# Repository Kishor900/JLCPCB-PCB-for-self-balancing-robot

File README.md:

# Self Balancing Robot PCB Board Powered by JLCPCB.COM
This repo conists of robotics project NON-Arduino version Self balancing robot PCB

# How to upload ?
1. Clone or download the gerber file from this repo
2. Open jlcpcb.com
3. Click `Quote Now` button and 
4. Click `Add you gerber file`
5. Everything is prettymuch ok if your settings are just decent enough
6. Select shipping method and add to cart

# Verification
JLCPCB professional team will verify your gerber files within an hour

Once verified they will ship your order that should reach you within 10-15 working days

# How to modify schematic and brd ?
To edit my schematic you are going to need Autodesk Eagle CAD software. Once installed, open my brd and schematic file and import them to a project.

Thank you :)

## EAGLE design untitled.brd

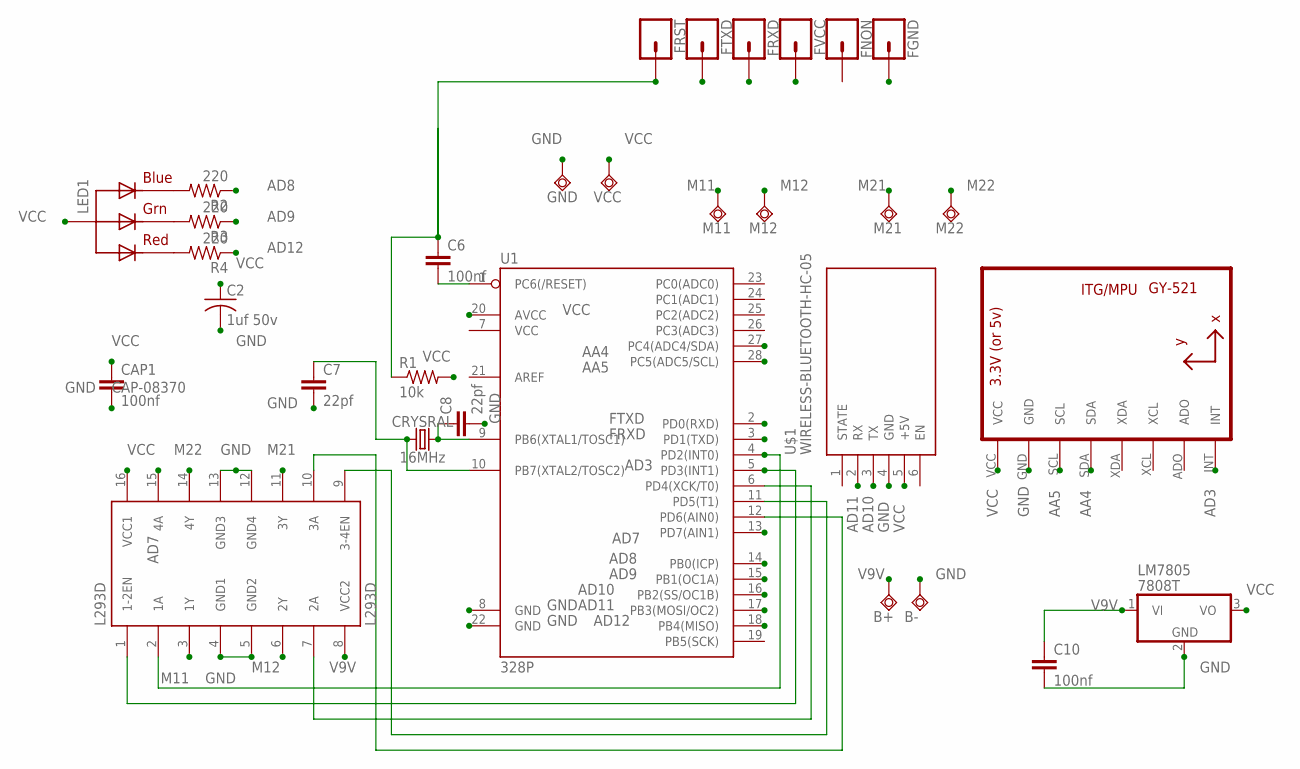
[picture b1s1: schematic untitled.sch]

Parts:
B+: TESTPAD_TPSQPAD1-20Y; TESTPAD_P1-20Y
B-: TESTPAD_TPSQPAD1-20Y; TESTPAD_P1-20Y
C2: 1uf 50v; C025-024X044
C6, C10: 100nf; CAP-PTH-SMALL-KIT
C7, C8: 22pf; CAP-PTH-SMALL-KIT
CAP1: 100nf; CAP-PTH-SMALL-KIT
CRYSRAL: 16MHz; HC49US
FGND: CONN_01; 1X01
FNON: CONN_01; 1X01
FRST: CONN_01; 1X01
FRXD: CONN_01; 1X01
FTXD: CONN_01; 1X01
FVCC: CONN_01; 1X01
GND: TESTPAD_TPSQB2,54; TESTPAD_B2,54
L293D: L293D; DIL16
LED1: RGBLED_CA-PIRANHA; PIRANHA5MM
LM7805: 7808T; TO220H
M11, M12, M21, M22: TESTPAD_TPSQPAD1-13; TESTPAD_P1-13
R1: 10k; 0204/7
R2, R3, R4: 220; 0204/7
U1: 328P; DIP28
U2: GY-521MPU6050; GY-521
U$1: WIRELESS-BLUETOOTH-HC-05
VCC: TESTPAD_TPSQB2,54; TESTPAD_B2,54

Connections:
AA4: U1.27 (PC4(ADC4/SDA)), U2.SDA
AA5: U1.28 (PC5(ADC5/SCL)), U2.SCL
AD3: L293D.1 (1-2EN), U1.5 (PD3(INT1)), U2.INT
AD7: L293D.15 (4A), U1.13 (PD7(AIN1))
AD8: R2.1, U1.14 (PB0(ICP))
AD9: R3.1, U1.15 (PB1(OC1A))
AD10: U1.16 (PB2(SS/OC1B)), U$1.3 (TX)
AD11: U1.17 (PB3(MOSI/OC2)), U$1.2 (RX)
AD12: R4.1, U1.18 (PB4(MISO))
FRXD: FRXD.1, U1.3 (PD1(TXD))
FTXD: FTXD.1, U1.2 (PD0(RXD))
GND: B-.TP, C2.2, C7.2, C8.2, C10.2, CAP1.2, FGND.1, GND.TP, L293D.4 (GND1), L293D.5 (GND2), L293D.12 (GND4), L293D.13 (GND3), LM7805.2 (GND), U1.8 (GND), U1.22 (GND), U2.GND, U$1.4 (GND)
M11: L293D.3 (1Y), M11.TP
M12: L293D.6 (2Y), M12.TP
M21: L293D.11 (3Y), M21.TP
M22: L293D.14 (4Y), M22.TP
unnamed: C6.2, U1.1 (PC6(/RESET))
unnamed: L293D.2 (1A), U1.4 (PD2(INT0))
unnamed: LED1.1 (BLUE), R2.2
unnamed: L293D.7 (2A), U1.6 (PD4(XCK/T0))
unnamed: C8.1, CRYSRAL.2, U1.9 (PB6(XTAL1/TOSC1))
unnamed: C7.1, CRYSRAL.1, U1.10 (PB7(XTAL2/TOSC2))
unnamed: L293D.9 (3-4EN), U1.11 (PD5(T1))
unnamed: L293D.10 (3A), U1.12 (PD6(AIN0))
unnamed: LED1.2 (RED), R4.2
unnamed: LED1.3 (GREEN), R3.2
unnamed: C6.1, FRST.1, R1.1
V9V: B+.TP, C10.1, L293D.8 (VCC2), LM7805.1 (VI)
VCC: C2.1, CAP1.1, FVCC.1, L293D.16 (VCC1), LED1.4 (VCC), LM7805.3 (VO), R1.2, U1.20 (AVCC), U2.VCC, U$1.5 (+5V), VCC.TP

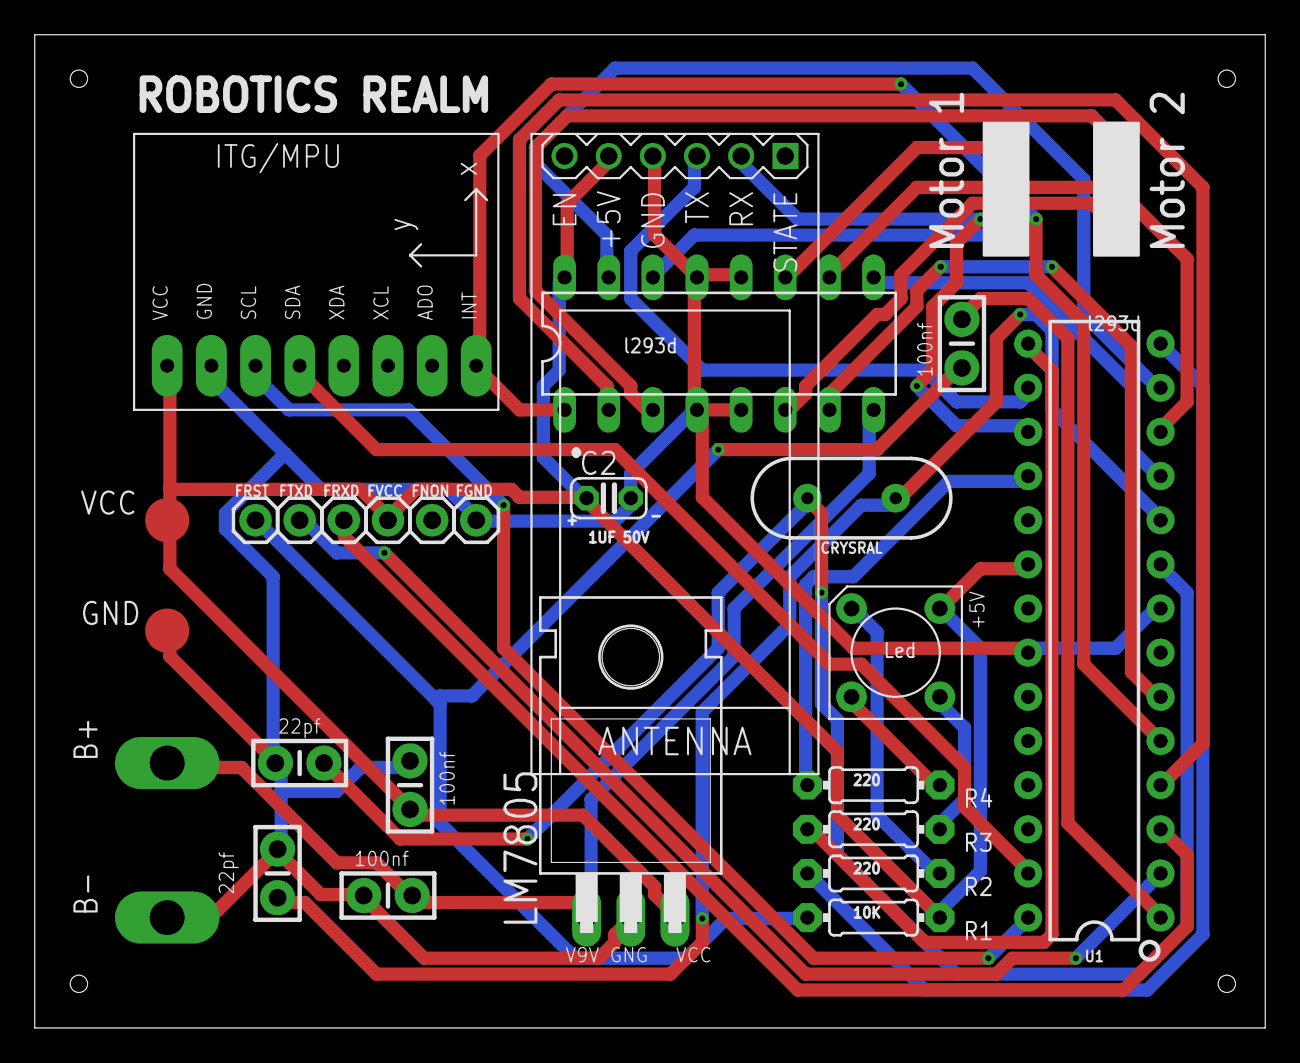
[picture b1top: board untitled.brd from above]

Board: 2 copper layers, 70.8 x 57.1 mm, 31 parts (0 on the bottom side), 29 nets.

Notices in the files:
parts and their libraries:
SparkFun-Capacitors: Licensing: Creative Commons ShareAlike 4.0 International - https://creativecommons.org/licenses/by-sa/4.0
diy-modules: Released under the Creative Commons Attribution 4.0 International License: http://creativecommons.org/licenses/by/4.0
